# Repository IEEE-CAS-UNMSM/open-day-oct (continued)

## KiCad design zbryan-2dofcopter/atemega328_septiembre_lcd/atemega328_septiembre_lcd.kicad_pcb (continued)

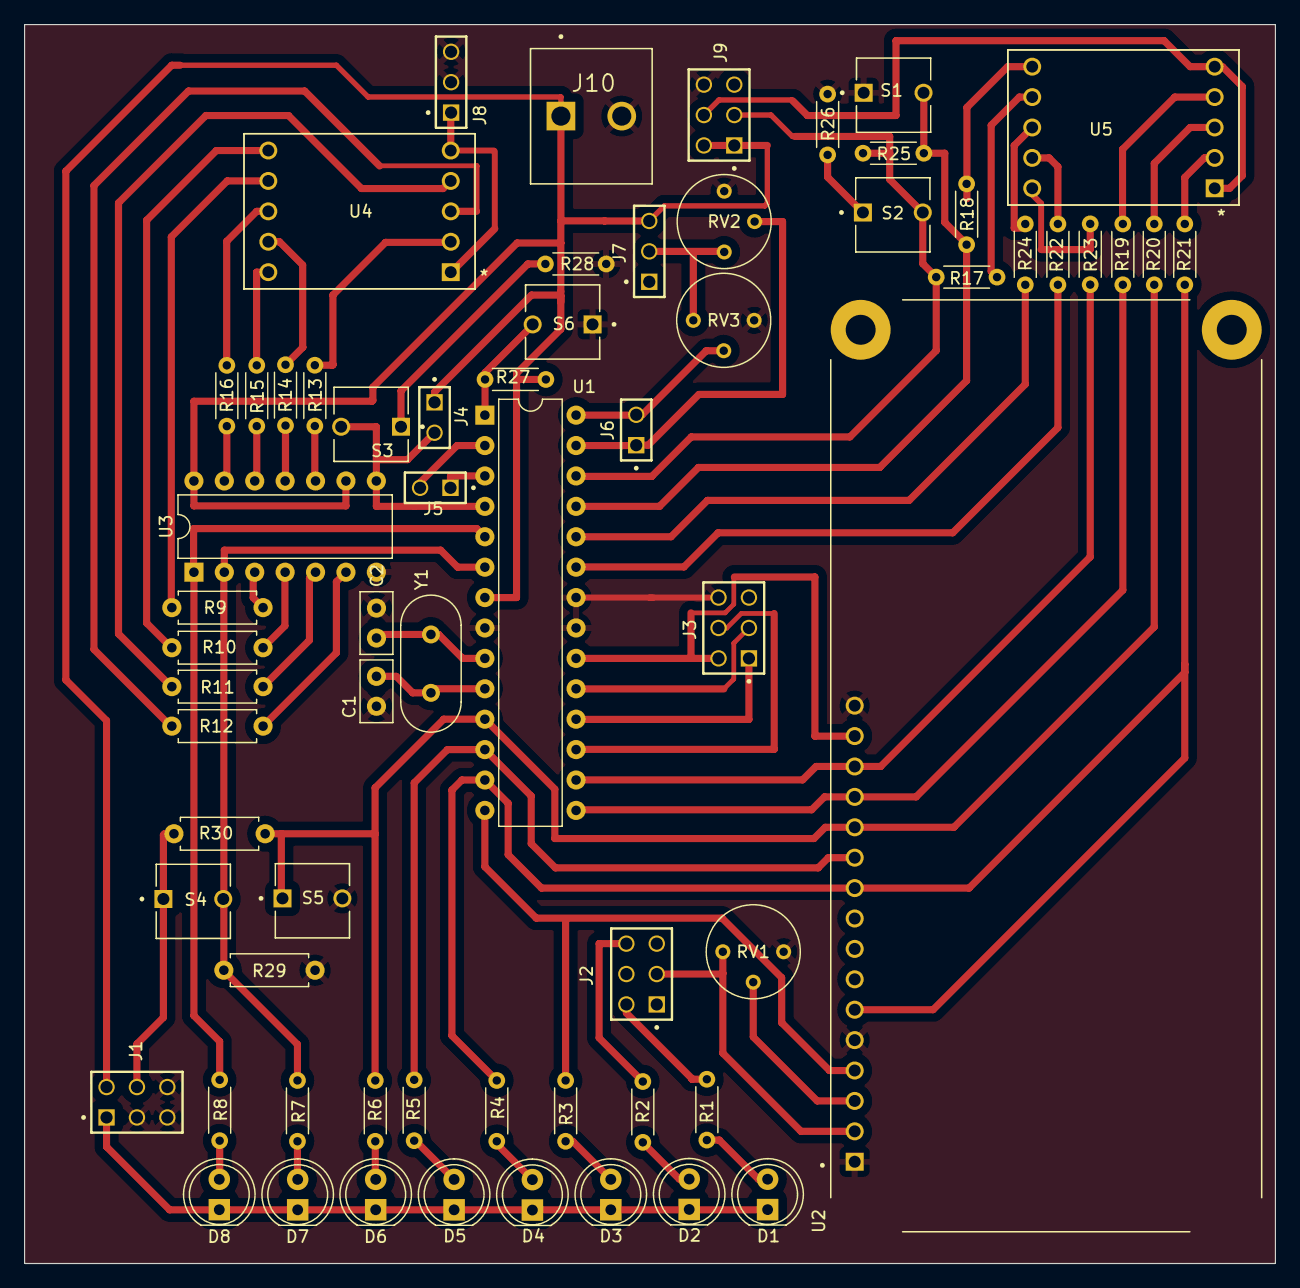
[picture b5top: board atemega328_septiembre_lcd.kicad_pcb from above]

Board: 2 copper layers, 104.5 x 103.5 mm, 65 parts (0 on the bottom side), 68 nets.
